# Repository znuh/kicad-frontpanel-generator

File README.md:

# KiCad Frontpanel Generator

KiCad Frontpanel Generator creates matching front panels for KiCad PCBs automatically. The PCB designer defines cut-outs and labels in unused layers of footprints and in the PCB. The Front Panel Generator then uses the shapes from these layers to generate a suitable cover plate.

## Why a web app instead of a KiCad Plugin?
When I made the initial prototype in 2025, the old plugin API was ~~dying~~ deprecated and the new API still struggling to be born. Creating a derivative of a PCB without replacing/overwriting the original PCB was not possible. I already had a KiCad PCB parser in JS from [another project](https://github.com/znuh/kicad-chm36), so I decided to build upon this. Also, this should make SVG output (laser-cut frontpanels!) easier.

## Status
**Warning:** This is work in progress. The UI still needs some improvement and more testing. There is no documentation or manual yet.  
**Supported KiCad versions: 9, 10**. Older versions *might* work, but the output will be a potentially faulty KiCad 9 PCB file.

## Example

## Trying it
You can see/try it here without cloning the repo: [znu.nz/fpgen](https://znu.nz/fpgen/)
1) Load *enc-hid_kicad-v10.kicad_pcb* from the examples directory in the FP generator
2) Save the resulting KiCad PCB
3) Load the saved file in KiCad / pcbnew

## Funding

This project is funded through [NGI0 Commons Fund](https://nlnet.nl/commonsfund), a fund established by [NLnet](https://nlnet.nl) with financial support from the European Commission's [Next Generation Internet](https://ngi.eu) program. Learn more at the [NLnet project page](https://nlnet.nl/project/Frontpanel-Generator).

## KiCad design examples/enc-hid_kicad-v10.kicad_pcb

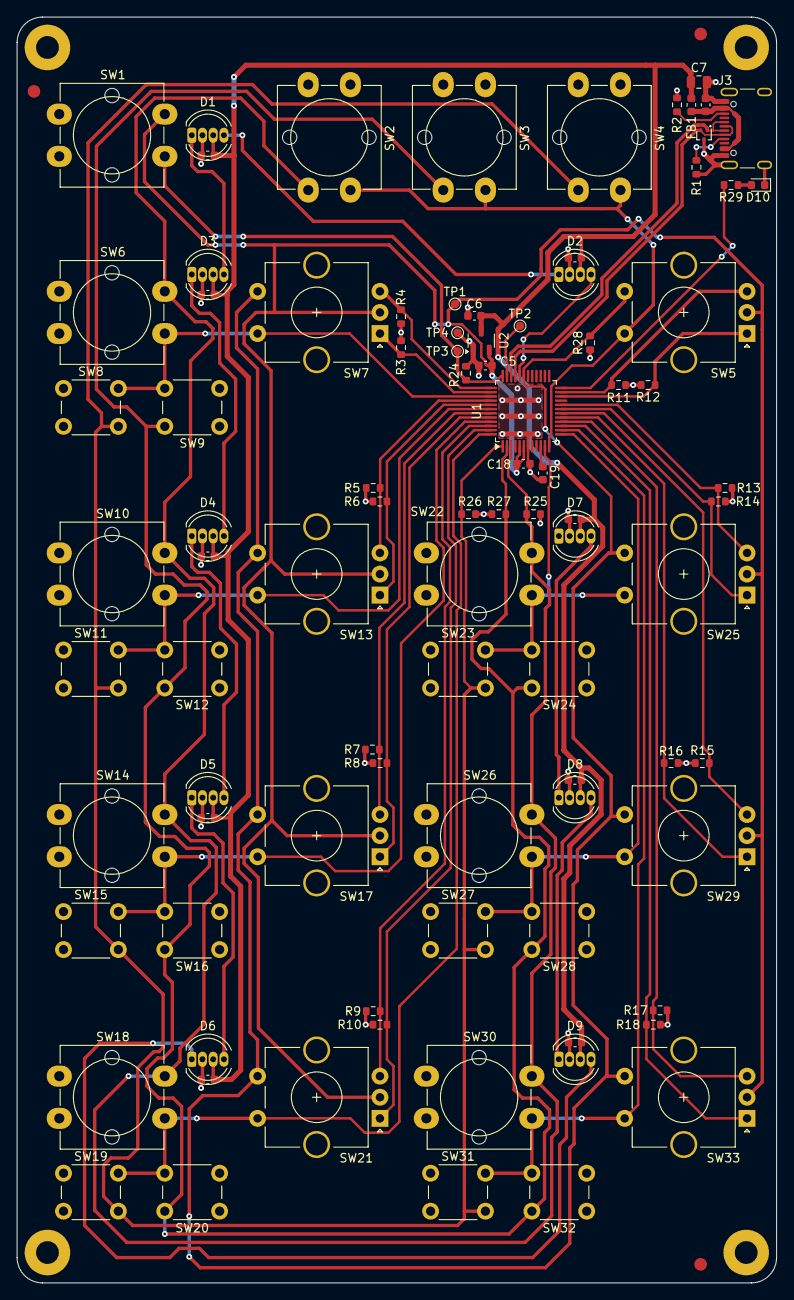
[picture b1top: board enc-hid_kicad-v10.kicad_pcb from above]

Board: 2 copper layers, 90.0 x 150.0 mm, 98 parts (0 on the bottom side), 50 nets.

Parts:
C1, C19: 0.1u; C_0603_1608Metric
C5, C6: 4.7uF/10V; C_0603_1608Metric
C7: 22uF/10V; C_0805_2012Metric
C8, C9, C10, C11, C12, C13, C14, C15, C16, C18: 4.7u; C_0603_1608Metric
D1, D2, D3, D4, D5, D6, D7, D8, D9: APA-106-F5; LED_D5.0mm-4_RGB
D10: LED; D_0603_1608Metric
D20: ESD5V3U2U; Infineon_PG-TSFP-3-1
FB1: FerriteBead; L_0603_1608Metric
FID1, FID2, FID3: Fiducial; Fiducial_1.5mm_Mask3mm
H1, H2, H3, H4: MountingHole; MountingHole_2.7mm_Pad
J3: USB_C_Receptacle_USB2.0_16P; USB_C_Receptacle_GCT_USB4105-xx-A_16P_TopMnt_Horizontal
R1, R2, R3, R4, R5, R6, R7, R8, R9, R10, R11, R12, R13, R14, R15, R16, R17, R18, R24, R25, R26, R27, R28, R29: 5.1k; R_0603_1608Metric
SW1, SW2, SW3, SW4, SW6, SW10, SW14, SW18, SW22, SW26, SW30: BTN 12mm; SW_PUSH-12mm_Wuerth-430476085716
SW5, SW7, SW13, SW17, SW21, SW25, SW29, SW33: EC11E; RotaryEncoder_Alps_EC11E-Switch_Vertical_H20mm_CircularMoun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
SW8, SW9, SW11, SW12, SW15, SW16, SW19, SW20, SW23, SW24, SW27, SW28, SW31, SW32: BTN 6mm; SW_PUSH_6mm_H9.5mm
TP1: Vtg; TestPoint_Pad_D1.0mm
TP2: SWDIO; TestPoint_Pad_D1.0mm
TP3: SWCLK; TestPoint_Pad_D1.0mm
TP4: GND; TestPoint_Pad_D1.0mm
U1: STM32C071CBTx; LQFP-48_7x7mm_P0.5mm
U2: AP7313-33SRG; SOT-23-3

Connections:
+3V3: C5.2, C18.1, SW1.1, SW5.C, SW7.C, SW13.C, SW17.C, SW21.C, SW25.C, SW29.C, SW33.C, TP1.1, U1.5 (VREF+), U1.6 (VDD), U2.2 (VO)
+5V: C6.2, C7.2, C8.1, C9.1, C10.1, C11.1, C12.1, C13.1, C14.1, C15.1, C16.1, D1.3 (VDD), D2.3 (VDD), D3.3 (VDD), D4.3 (VDD), D5.3 (VDD), D6.3 (VDD), D7.3 (VDD), D8.3 (VDD), D9.3 (VDD), FB1.2, U2.3 (VI)
/DO2: D1.4 (DI), D2.1 (DO)
/MCU USB/PA13_SWDIO: TP2.1, U1.35 (PA13)
/MCU USB/USB_N: D20.2, J3.A7 (D-), J3.B7 (D-), U1.33 (PA11)
/MCU USB/USB_P: D20.1, J3.A6 (D+), J3.B6 (D+), U1.34 (PA12)
/MCU USB/VUSB: C1.1, FB1.1, J3.A4 (VBUS), J3.A9 (VBUS), J3.B4 (VBUS), J3.B9 (VBUS)
/MCU USB/~RST: C19.1, U1.10 (PF2)
B1: R25.2, SW2.2, SW6.1, SW10.1, SW14.1, SW18.1, SW22.1, SW26.1, SW30.1, U1.3 (PC15)
B2: R26.2, SW4.2, SW8.2, SW11.2, SW15.2, SW19.2, SW23.2, SW27.2, SW31.2, U1.1 (PC13)
B3: R27.2, SW3.2, SW9.1, SW12.1, SW16.1, SW20.1, SW24.1, SW28.1, SW32.1, U1.2 (PC14)
B4: R28.2, SW5.S1, SW7.S1, SW13.S1, SW17.S1, SW21.S1, SW25.S1, SW29.S1, SW33.S1, U1.31 (PC7)
E1A: R3.1, SW7.A, U1.38 (PD0)
E1B: R4.1, SW7.B, U1.37 (PA15)
E2A: R6.1, SW13.A, U1.41 (PD3)
E2B: R5.1, SW13.B, U1.40 (PD2)
E3A: R8.1, SW17.A, U1.44 (PB5)
E3B: R7.1, SW17.B, U1.43 (PB4)
E4A: R10.1, SW21.A, U1.47 (PB8)
E4B: R9.1, SW21.B, U1.46 (PB7)
E5A: R12.1, SW5.A, U1.22 (PB10)
E5B: R11.1, SW5.B, U1.23 (PB11)
E6A: R14.1, SW25.A, U1.19 (PB0)
E6B: R13.1, SW25.B, U1.20 (PB1)
E7A: R16.1, SW29.A, U1.17 (PA6)
E7B: R15.1, SW29.B, U1.18 (PA7)
E8A: R18.1, SW33.A, U1.15 (PA4)
E8B: R17.1, SW33.B, U1.16 (PA5)
G1: SW6.2, SW7.S2, SW8.1, SW9.2, U1.39 (PD1)
G2: SW10.2, SW11.1, SW12.2, SW13.S2, U1.42 (PB3)
G3: SW14.2, SW15.1, SW16.2, SW17.S2, U1.45 (PB6)
G4: SW18.2, SW19.1, SW20.2, SW21.S2, U1.48 (PB9)
G5: SW2.1, SW3.1, SW4.1, SW5.S2, U1.12 (PA1)
G6: SW22.2, SW23.1, SW24.2, SW25.S2, U1.11 (PA0)
G7: SW26.2, SW27.1, SW28.2, SW29.S2, U1.13 (PA2)
G8: SW30.2, SW31.1, SW32.2, SW33.S2, U1.14 (PA3)
GND: C1.2, C5.1, C6.1, C7.1, C8.2, C9.2, C10.2, C11.2, C12.2, C13.2, C14.2, C15.2, C16.2, C18.2, C19.2, D1.2 (GND), D2.2 (GND), D3.2 (GND), D4.2 (GND), D5.2 (GND), D6.2 (GND), D7.2 (GND), D8.2 (GND), D9.2 (GND), D10.1 (K), D20.3 (GND), H1.1, H2.1, H3.1, H4.1, J3.A1 (GND), J3.A12 (GND), J3.B1 (GND), J3.B12 (GND), J3.S1 (SHIELD), R1.2, R2.2, R3.2, R4.2, R5.2, R6.2, R7.2, R8.2, R9.2, R10.2, R11.2, R12.2, R13.2, R14.2, R15.2, R16.2, R17.2, R18.2, R24.1, R25.1, R26.1, R27.1, R28.1, SW5.MP, SW7.MP, SW13.MP, SW17.MP, SW21.MP, SW25.MP, SW29.MP, SW33.MP, TP4.1, U1.7 (VSS), U2.1 (GND)
MOSI2: D2.4 (DI), U1.32 (PA10)
unnamed: D1.1 (DO), D3.4 (DI)
unnamed: D3.1 (DO), D4.4 (DI)
unnamed: D4.1 (DO), D5.4 (DI)
unnamed: D5.1 (DO), D6.4 (DI)
unnamed: D6.1 (DO), D9.4 (DI)
unnamed: D7.4 (DI), D8.1 (DO)
unnamed: D8.4 (DI), D9.1 (DO)
unnamed: D10.2 (A), R29.1
unnamed: J3.A5 (CC1), R1.1
unnamed: J3.B5 (CC2), R2.1
unnamed: R29.2, U1.24 (PB12)
SW1: R24.2, SW1.2, TP3.1, U1.36 (PA14)

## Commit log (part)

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2026-04-09 Update README.md
    WIP
2026-04-09 Update README.md
    add NLnet funding notice
2026-04-09 import preexisting code
2026-04-09 Update README.md
    proper README
2026-05-18 add example PCB
2026-05-18 move JS files to extra dir, add Bootstrap
2026-05-18 switch to Bootstrap
2026-05-18 work on dark/light theme support
2026-05-18 Dark/light theme switching
2026-05-18 split UI into 3 cards: 1) File Input, 2) Config and 3) Output
2026-05-18 improve file upload
2026-05-18 make text more readable
2026-05-18 fancy schmancy drag&drop zone for file input
2026-06-13 make download button nicer
2026-06-13 working on layer mapping table
2026-06-13 add unused col
2026-06-13 trying drop down list
2026-06-13 checkboxes directly in table row
2026-06-13 better keep it simple...
2026-06-13 settings for 3d models
2026-06-23 remove UI test elements
2026-06-23 working on kicad layer mapping table
2026-06-23 make output layer options in mapping table
2026-06-23 remove leftover test options
2026-06-23 add TODOs
2026-06-23 UI config working
2026-06-23 sanitize z_ofs input
2026-06-23 prepare for kicad v10 support
2026-06-23 add KiCad v10 input example
2026-06-23 add version and source repo link in web page
2026-06-23 Update README.md: Status update
2026-06-24 give the user feedback when they try loading an unsuitable file
